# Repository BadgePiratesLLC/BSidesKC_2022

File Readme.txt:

BSidesKC 2022 Website: https://bsideskc.org/

Date: September 23-24, 2021 | PlexPod Westport| Kansas City, MO

LED Layout
------------------
io03 - D1 - "B"
io34 - D2 - "S"
io04 - D3 - "I"
io33 - D4 - "D"
io05 - D5 - "E"
io26 - D6 - "S" (second S)
io06 - D7 - "0"
io21 - D8 - "1" 
io14 - D9 - "2"
io35 - D10 - "3"
io10 - D11 - "4"
io15 - D13 - "5"
io36 - D14 - "6"
io11 - D15 - "7"
io16 - D17 - "8"
io37 - D18 - "9"
io12 - D19 - "10"
io17 - D20 - "11"

Rotary A - 38
Rotary B - 13
Rotary Switch - 7

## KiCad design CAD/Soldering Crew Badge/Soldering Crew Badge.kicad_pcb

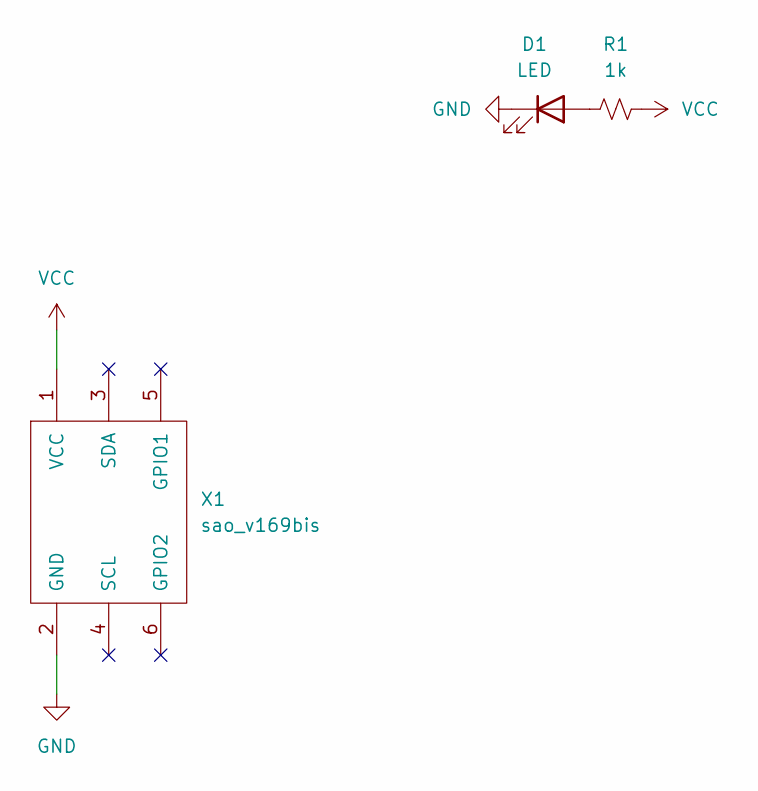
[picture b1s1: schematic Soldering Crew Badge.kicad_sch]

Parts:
D1: LED; LED_Osram_Lx_P47F_D2mm_ReverseMount_Proper_Mask Only
R1: 1k; R_1206_3216Metric
X1: sao_v169bis; Badgelife-SAOv169-SAO_Side_B.SLK

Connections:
GND: D1.1 (K), X1.2 (GND)
unnamed: D1.2 (A), R1.1
VCC: R1.2, X1.1 (VCC)

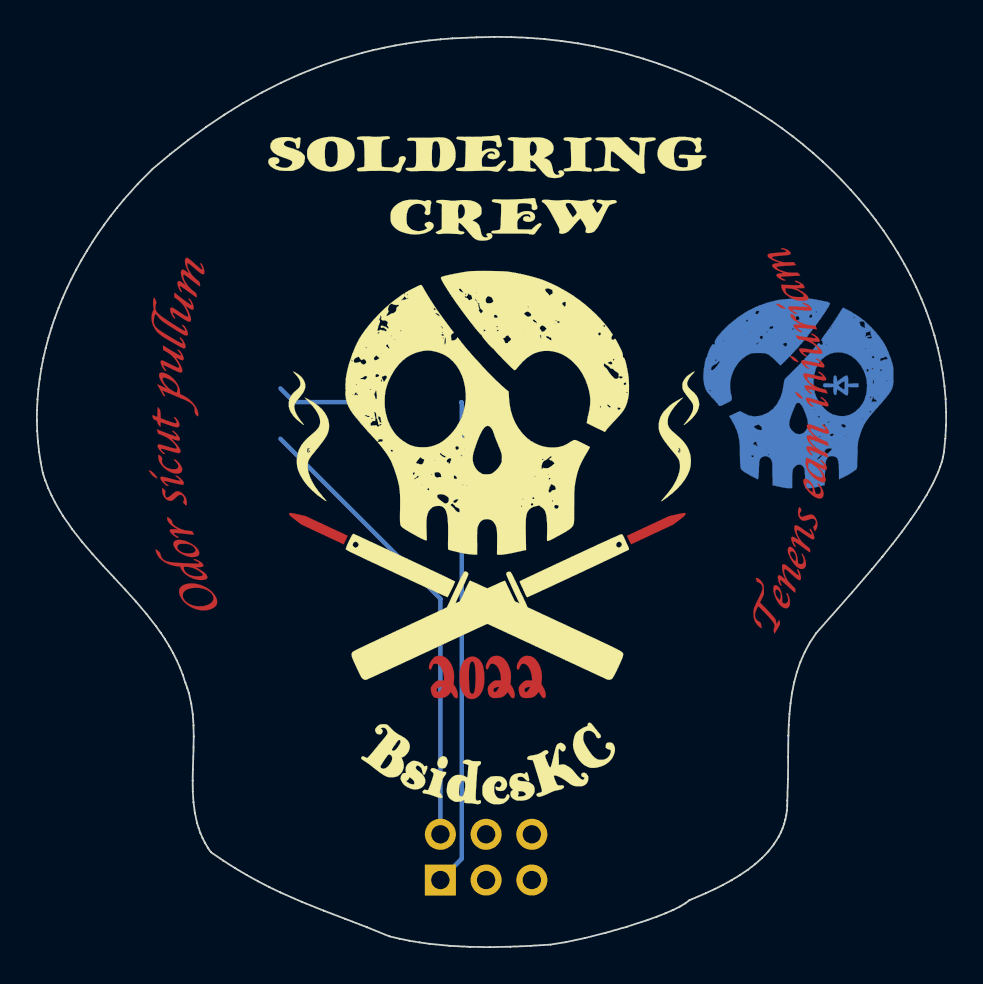
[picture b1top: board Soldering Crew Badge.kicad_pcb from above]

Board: 2 copper layers, 50.5 x 50.6 mm, 3 parts (1 on the bottom side), 3 nets.

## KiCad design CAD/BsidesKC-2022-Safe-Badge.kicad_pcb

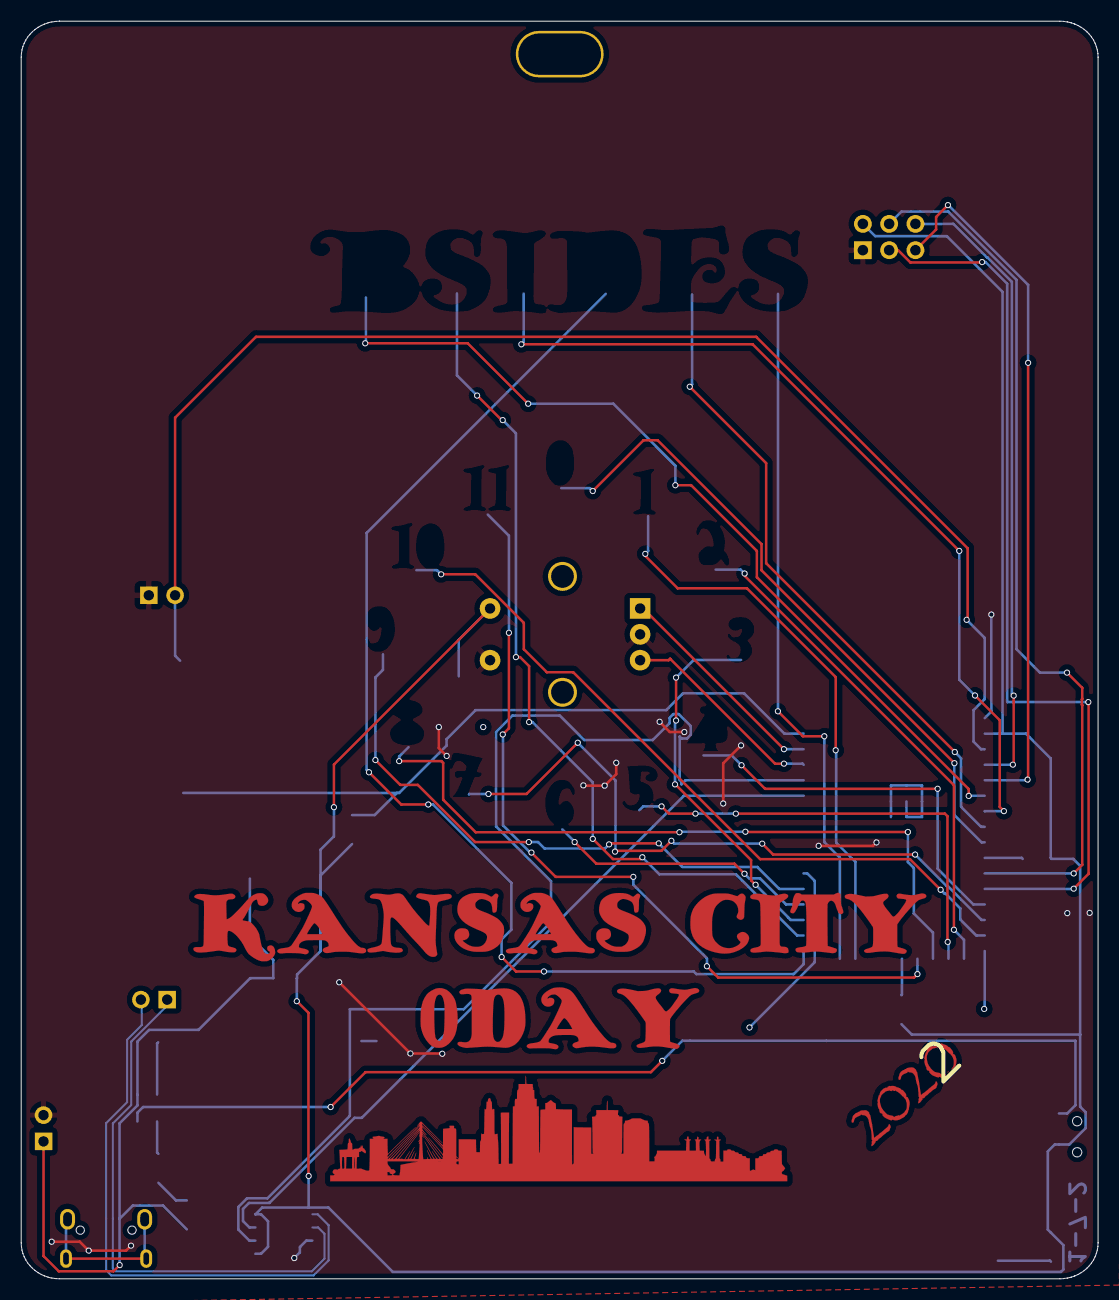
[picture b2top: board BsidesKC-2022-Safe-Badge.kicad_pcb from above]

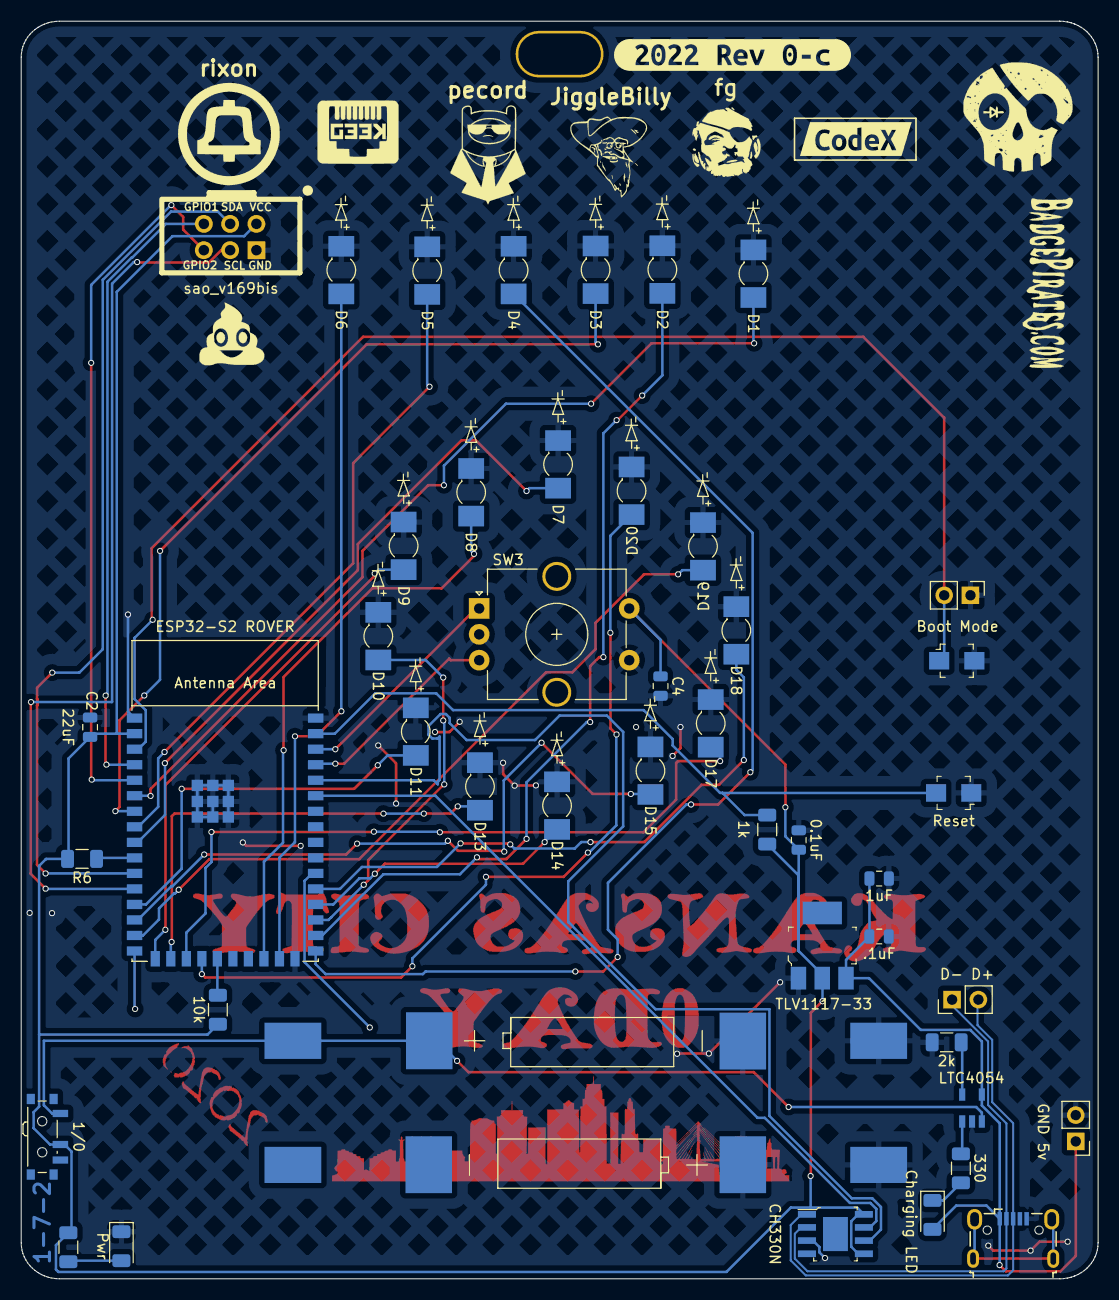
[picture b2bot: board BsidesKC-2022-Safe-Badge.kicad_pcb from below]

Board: 2 copper layers, 104.1 x 121.5 mm, 47 parts (28 on the bottom side), 40 nets.

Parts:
1/0: SW_SPDT; SW_SPDT_PCM12
BT1: Battery; AA
C1: 1uF; C_0805_2012Metric
C2: 22uF; C_0805_2012Metric
C3: 0.1uF; C_0805_2012Metric
C4, C5: .1uF; C_0805_2012Metric
D1, D2, D3, D4, D5, D6, D7, D8, D9, D10, D11, D13, D14, D15, D17, D18, D19, D20: LED; LED_Osram_Lx_P47F_D2mm_ReverseMount_Proper_Mask Only
D12: Charging LED; LED_1206_3216Metric
D16: Pwr; LED_1206_3216Metric
D- D+: Conn_01x02_Female; PinHeader_1x02_P2.54mm_Vertical
ESP32-S2 ROVER: ESP32-S2-WROOM; ESP32-S2-WROVER
GND 5v: 1x2; PinHeader_1x02_P2.54mm_Vertical
J2: 1x2; PinHeader_1x02_P2.54mm_Vertical
J4: USB_B_Mini; USB_Micro-B_Wuerth
R1: 2k; R_1206_3216Metric
R2: 330; R_1206_3216Metric
R3: R; R_1206_3216Metric
R4: 1k; R_1206_3216Metric
R5: 10k; R_1206_3216Metric
R6: R_Small_US; R_1206_3216Metric
Reset: Reset_Btn; Switch_Tactile_SMD_B3U-1000P-BPVersion
SW2: Boot Mode; Switch_Tactile_SMD_B3U-1000P-BPVersion
SW3: RotaryEncoder_Switch; RotaryEncoder_Alps_EC12E-Switch_Vertical_H20mm_CircularMoun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
U1: LTC4054
U3: CH330N; SOIC-8-1EP_W3.9mm
U4: TLV1117-33; SOT-223
X1: sao_v169bis; Badgelife-SAOv169-SAO_Side_B.SLK
kibuzzard-62C240C4: G***; kibuzzard-62C240C4
kibuzzard-62FC3E66: G***; kibuzzard-62FC3E66

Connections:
Boot: ESP32-S2 ROVER.3 (IO00), J2.2, SW2.1 (A)
D+: D- D+.2, J4.3 (D+), U3.1 (UD+)
D-: D- D+.1, J4.2 (D-), U3.2 (UD-)
GND: BT1.2 (-), C1.2, C2.2, C3.2, C4.2, C5.2, D1.1 (K), D2.1 (K), D3.1 (K), D4.1 (K), D5.1 (K), D6.1 (K), D7.1 (K), D8.1 (K), D9.1 (K), D10.1 (K), D11.1 (K), D13.1 (K), D14.1 (K), D15.1 (K), D16.1 (K), D17.1 (K), D18.1 (K), D19.1 (K), D20.1 (K), ESP32-S2 ROVER.1 (GND), ESP32-S2 ROVER.26 (GND), ESP32-S2 ROVER.42 (GND), ESP32-S2 ROVER.43 (GND), GND 5v.2, J2.1, J4.5 (GND), R1.2, Reset.1 (C), SW2.2 (B), SW3.C, SW3.S2, U1.2 (GND), U3.3 (GND), U4.1 (GND), X1.2 (GND)
IO01: ESP32-S2 ROVER.4 (IO01), X1.5 (GPIO1)
IO02: ESP32-S2 ROVER.5 (IO02), X1.6 (GPIO2)
IO03: D1.2 (A), ESP32-S2 ROVER.6 (IO03)
IO04: D3.2 (A), ESP32-S2 ROVER.7 (IO04)
IO05: D5.2 (A), ESP32-S2 ROVER.8 (IO05)
IO06: D7.2 (A), ESP32-S2 ROVER.9 (IO06)
IO07: ESP32-S2 ROVER.10 (IO07), R6.1
IO08: ESP32-S2 ROVER.11 (IO08), X1.3 (SDA)
IO09: ESP32-S2 ROVER.12 (IO09), X1.4 (SCL)
IO10: D11.2 (A), ESP32-S2 ROVER.13 (IO10)
IO11: D15.2 (A), ESP32-S2 ROVER.14 (IO11)
IO12: D19.2 (A), ESP32-S2 ROVER.15 (IO12)
IO14: D9.2 (A), ESP32-S2 ROVER.17 (IO14)
IO15: D13.2 (A), ESP32-S2 ROVER.18 (IO15)
IO16: D17.2 (A), ESP32-S2 ROVER.19 (IO16)
IO17: D20.2 (A), ESP32-S2 ROVER.20 (IO17)
IO21: D8.2 (A), ESP32-S2 ROVER.24 (IO21)
IO26: D6.2 (A), ESP32-S2 ROVER.25 (IO26)
IO33: D4.2 (A), ESP32-S2 ROVER.27 (IO33)
IO34: D2.2 (A), ESP32-S2 ROVER.28 (IO34)
IO35: D10.2 (A), ESP32-S2 ROVER.29 (IO35)
IO36: D14.2 (A), ESP32-S2 ROVER.30 (IO36)
IO37: D18.2 (A), ESP32-S2 ROVER.31 (IO37)
IO45: ESP32-S2 ROVER.39 (IO45), SW3.B
IO46: ESP32-S2 ROVER.40 (IO46), SW3.A
unnamed: 1/0.1 (A), BT1.1 (+), U1.3 (BAT)
unnamed: D12.1 (K), R2.1
unnamed: D16.2 (A), R3.2
unnamed: R1.1, U1.5 (PROG)
unnamed: R2.2, U1.1 (~CHRG)
unnamed: ESP32-S2 ROVER.21 (IO18), R5.1
RESET: ESP32-S2 ROVER.41 (EN), R4.2, Reset.2 (D)
USB_RX_ESP_TX: ESP32-S2 ROVER.37 (TXD0), U3.7 (RXD)
USB_TX_ESP_RX: ESP32-S2 ROVER.38 (RXD0), U3.6 (TXD)
VBUS: C1.1, C5.1, D12.2 (A), GND 5v.1, J4.1 (VBUS), U1.4 (VCC), U4.3 (VI)
VCC: 1/0.2 (B), C2.1, C3.1, C4.1, ESP32-S2 ROVER.2 (3V3), R3.1, R4.1, R5.2, R6.2, SW3.S1, U3.5 (VCC), U3.8 (V3), U4.2 (VO), X1.1 (VCC)

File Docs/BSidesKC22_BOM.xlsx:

Id | DNP | Description | Package | Quantity | Designation | Supplier and ref | Supplier #2 | Cost (at scale) | 1-200 | Total Cost | Notes
1 |  | Resister | R_1206_3216Metric | 20 | 1k |  |  | 0.02 | 0.05 | 0.4
2 | Y |  | PinHeader_1x04_P2.54mm_Vertical | 1 | BottomToTop#1 |  |  |  |  | 0
3 |  | Capacitor | C_0805_2012Metric | 1 | 1uF |  |  | 0.05 | 0.1 | 0.05
4 |  | Resister | R_1206_3216Metric | 1 | 10k |  |  | 0.02 | 0.05 | 0.02
5 |  | LED | LED_1206_3216Metric (yellow) | 1 | Charging |  | https://lcsc.com/search?q=LED%201206 | 0.01 | 0.23 | 0.01
6 |  | MCU | ESP32-S2-WROOM | 1 | ESP32-S2-WROVER | <LUCY> |  | 2.9 | 2.9 | 2.9
7 | Y |  | PinHeader_1x02_P2.54mm_Vertical | 1 | 5v GND |  |  |  |  | 0
8 |  | LED | XZMYK45WT-9 | 18 | LED | https://www.digikey.com/en/products/detail/sunled/XZMYK45WT-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 |  | 0.18 | 0.25 | 3.2399999999999998
9 |  | Push Button | Switch_Tactile_SMD_B3U-1000P | 1 | Reset |  | https://lcsc.com/product-detail/Tactile-Switches_Omron-Elect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 | 0.45 | 0.5 | 0.45
10 | Y |  | PinHeader_1x02_P2.54mm_Vertical | 1 | D+ D- |  |  |  |  | 0
11 |  | Capacitor | C_0805_2012Metric | 3 | 0.1uF |  |  | 0.05 | 0.1 | 0.15000000000000002
12 |  | IC | SOT-223 | 1 | TLV1117-33 | https://www.mouser.com/c/?q=TLV1117-33 | https://lcsc.com/search?q=TLV1117-33 | 0.23 | 0.5 | 0.23
13 | Y |  | FG_B.SILK | 2 | fg |  |  |  |  | 0
14 |  | USB Connector | USB_Micro-B_Wuerth | 1 | USB_B_Mini | https://www.digikey.com/en/products/detail/w%C3%BCrth-elektr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 | Need another | 1.42 | 1.42 | 1.42
15 | Y |  | PinHeader_1x04_P2.54mm_Vertical | 1 | JTAG |  |  |  |  | 0
16 |  | Battery Holder | AA | 2 | Battery | https://www.digikey.com/en/products/detail/keystone-electron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 |  | 0.25 |  | 0.5
16.100000000000001 |  | Battery | 14500 Battery | 1 | Battery |  |  | ? | ? | ? | need to find
17 |  | Slide Switch | SW_SPDT_PCM12 | 1 | SW_SPDT |  | https://lcsc.com/product-detail/Slide-Switches_C-K-PCM12SMTR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 | 0.48 | 0.5 | 0.48
18 |  | IC | SOIC-8-1EP_W3.9mm | 1 | CH330N | <LUCY> |  | 0.38 | 0.38 | 0.38
19 |  | Resister | R_1206_3216Metric | 1 | 330 |  |  | 0.02 | 0.05 | 0.02
20 |  | Slide Switch | Switch_Tactile_SMD_B3U-1000P | 1 | Boot |  | https://lcsc.com/product-detail/Tactile-Switches_Omron-Elect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 | 0.45 | 0.5 | 0.45
21 | Y |  | BPSkull_Distressed_B.SILK | 2 | BP Logo |  |  |  |  | 0
22 |  | IC | MCP73831 | 1 | MCP73831 | https://www.mouser.com/c/?q=mcp%2073831 | https://lcsc.com/product-detail/Battery-Management-ICs_Micro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 | 0.57999999999999996 | 0.69 | 0.57999999999999996
23 | Y |  | BadgePiratesURL_B.SLK | 2 | LOGO |  |  |  |  | 0
24 | Y |  | PinHeader_1x02_P2.54mm_Vertical | 1 | Boot Jumper |  |  |  |  | 0
25 | Y |  | Badgelife-SAOv169-SAO_Side_B.SLK | 1 | sao_v169bis |  |  |  |  | 0
26 |  | Capacitor | C_0805_2012Metric | 1 | 22uF |  |  | 0.05 | 0.1 | 0.05
27 |  | Resister | R_1206_3216Metric | 1 | 2k |  |  | 0.02 | 0.06 | 0.02
28 |  | LED | LED_1206_3216Metric (Green) | 1 | Pwr |  |  | 0.01 | 0.25 | 0.01
29 | Y |  | PinHeader_1x04_P2.54mm_Vertical | 1 | TopToBottom#2 |  |  |  |  | 0
 |  |  |  |  |  |  |  | Just Board Cost |  |  | 0 |  | 0 | 0 | 0
 |  |  |  |  |  |  |  | Profit |  |  | 0 |  | 0 | 0 | 0

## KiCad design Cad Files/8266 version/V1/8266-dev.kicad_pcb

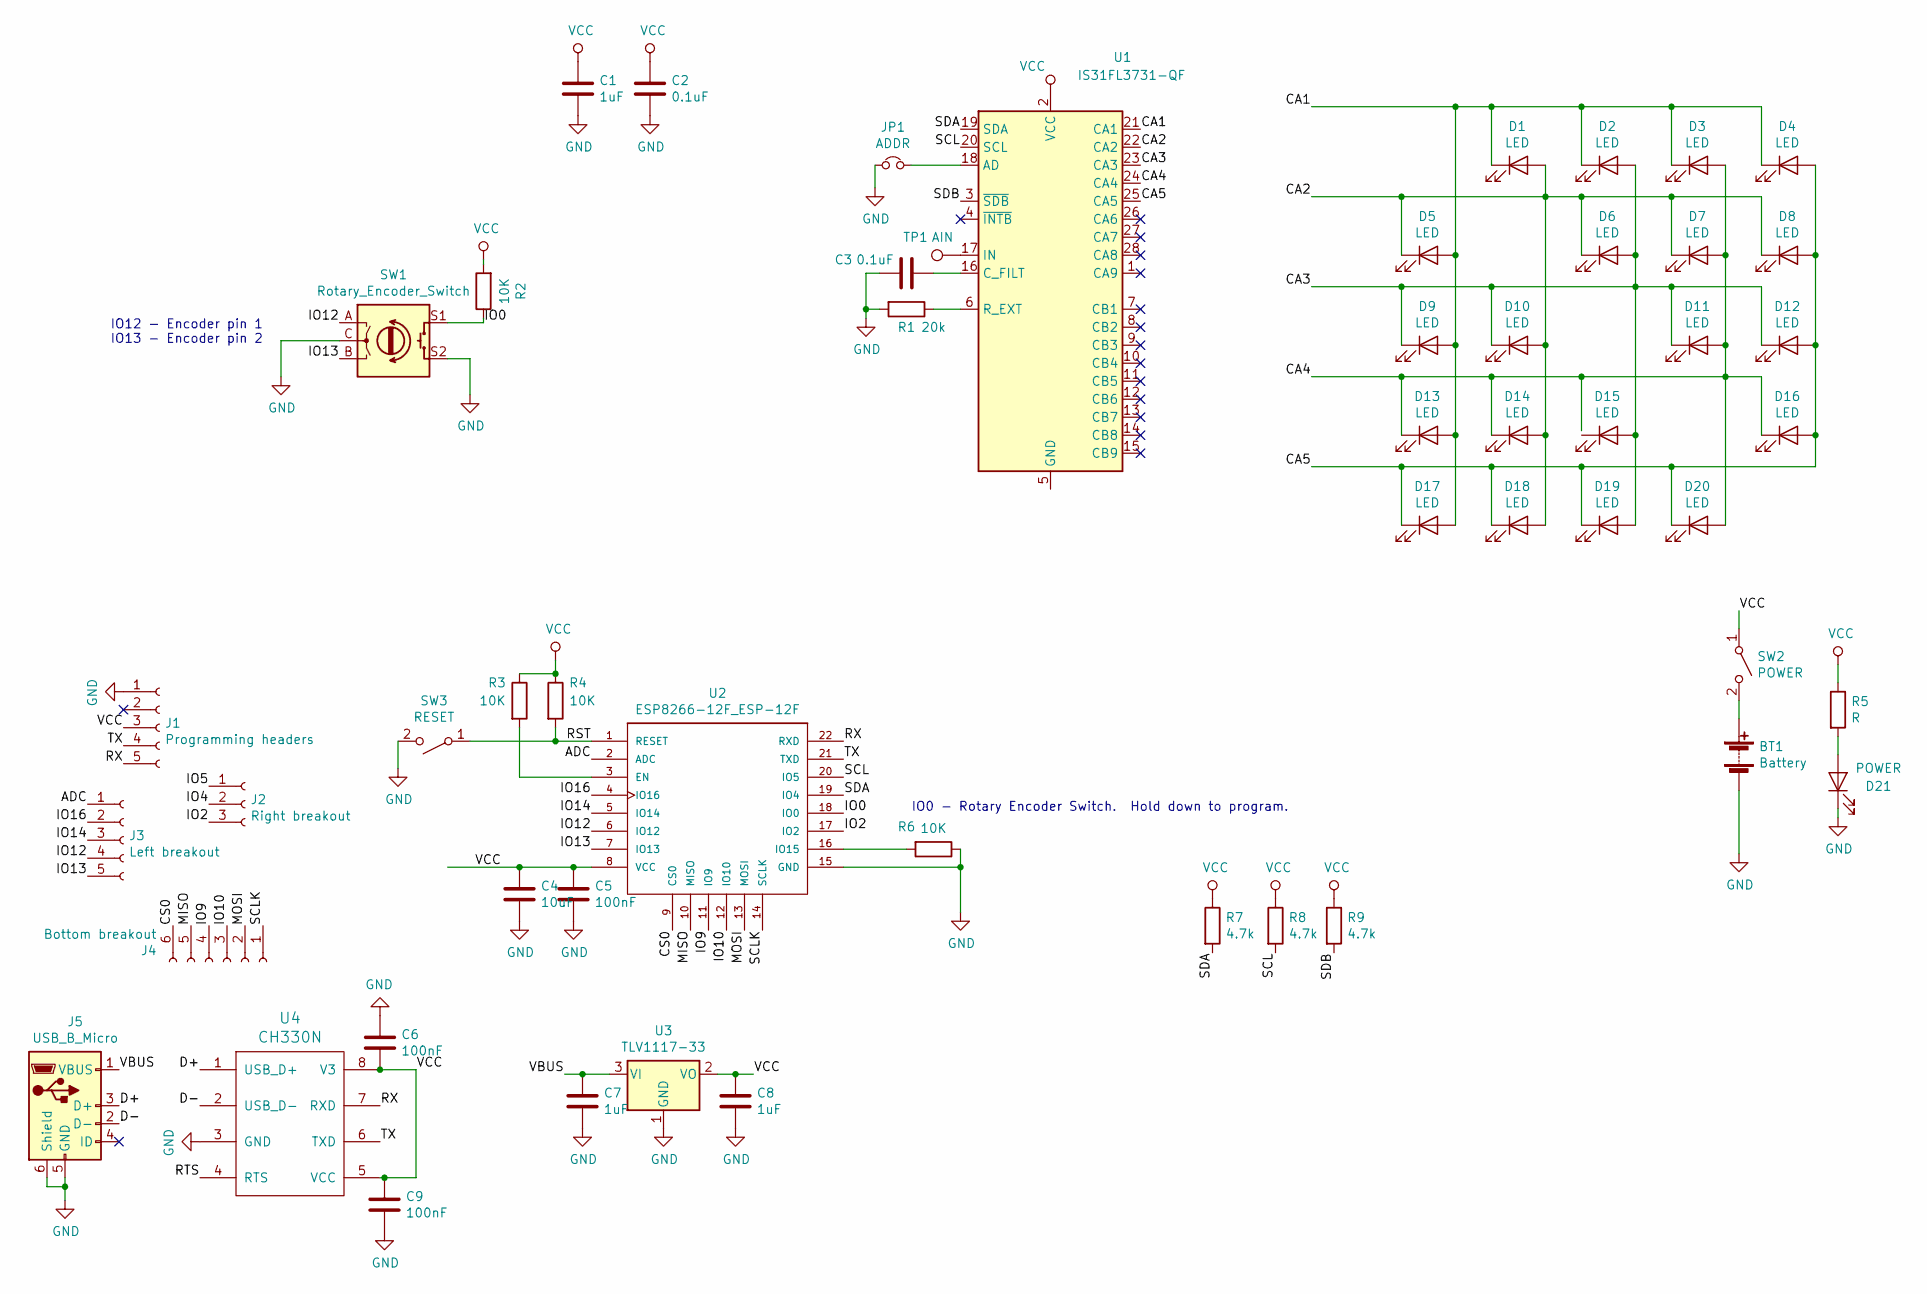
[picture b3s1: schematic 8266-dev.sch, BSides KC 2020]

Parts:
BT1: Battery; BatteryHolder_MPD_BC2003_1x2032
C1, C7, C8: 1uF; C_1206_3216Metric
C2, C3: 0.1uF; C_1206_3216Metric
C4: 10uF; C_1206_3216Metric
C5, C6, C9: 100nF; C_1206_3216Metric
D1, D2, D3, D4, D5, D6, D7, D8, D9, D10, D11, D12, D13, D14, D15, D16, D17, D18, D19, D20: LED; LED_Osram_Lx_P47F_D2mm_ReverseMount
D21: POWER; LED_1206_3216Metric_Pad1.42x1.75mm_HandSolder
J1: Programming headers; PinHeader_1x5_P2.5mm_Drill1.1mm
J2: Right breakout; PinHeader_1x3_P2.54_Drill1.1mm
J3: Left breakout; PinHeader_1x5_P2.5mm_Drill1.1mm
J4: Bottom breakout; PinHeader_1x06_P2.54mm_Vertical
J5: USB_B_Micro; USB_Micro-B_Molex-105017-0001
JP1: ADDR; SolderJumper-2_P1.3mm_Bridged_Pad1.0x1.5mm
R1: 20k; R_1206_3216Metric
R2, R3, R4, R6: 10K; R_1206_3216Metric
R5: R; R_1206_3216Metric
R7, R8, R9: 4.7k; R_1206_3216Metric
SW1: Rotary_Encoder_Switch; RotaryEncoder_Alps_EC12E-Switch_Vertical_H20mm_CircularMoun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
SW2: POWER; SW_SPDT_PCM12
SW3: RESET; SW_Push_1P1T_NO_6x6mm_H9.5mm
TP1: AIN; TestPoint_Pad_D2.0mm
U1: IS31FL3731-QF; QFN-28-1EP_4x4mm_P0.4mm_EP2.3x2.3mm
U2: ESP8266-12F_ESP-12F; XCVR_ESP8266-12E%2fESP-12E
U3: TLV1117-33; SOT-223-3_TabPin2
U4: CH330N; SOIC-8_3.9x4.9mm_P1.27mm

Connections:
/ADC: J3.1, U2.2 (ADC)
/CA1: D1.1 (K), D2.1 (K), D3.1 (K), D4.1 (K), D5.2 (A), D9.2 (A), D13.2 (A), D17.2 (A), U1.21 (CA1)
/CA2: D1.2 (A), D5.1 (K), D6.1 (K), D7.1 (K), D8.1 (K), D10.2 (A), D14.2 (A), D18.2 (A), U1.22 (CA2)
/CA3: D2.2 (A), D6.2 (A), D9.1 (K), D10.1 (K), D11.1 (K), D12.1 (K), D15.2 (A), D19.2 (A), U1.23 (CA3)
/CA4: D3.2 (A), D7.2 (A), D11.2 (A), D13.1 (K), D14.1 (K), D16.1 (K), D20.2 (A), U1.24 (CA4)
/CA5: D4.2 (A), D8.2 (A), D12.2 (A), D16.2 (A), D17.1 (K), D18.1 (K), D19.1 (K), D20.1 (K), U1.25 (CA5)
/CS0: J4.6, U2.9 (CS0)
/D+: J5.3 (D+), U4.1 (USB_D+)
/D-: J5.2 (D-), U4.2 (USB_D-)
/IO0: R2.1, SW1.S1, U2.18 (IO0)
/IO2: J2.3, U2.17 (IO2)
/IO9: J4.4, U2.11 (IO9)
/IO10: J4.3, U2.12 (IO10)
/IO12: J3.4, SW1.A, U2.6 (IO12)
/IO13: J3.5, SW1.B, U2.7 (IO13)
/IO14: J3.3, U2.5 (IO14)
/IO16: J3.2, U2.4 (IO16)
/MISO: J4.5, U2.10 (MISO)
/MOSI: J4.2, U2.13 (MOSI)
/RST: R4.2, SW3.1 (A), U2.1 (RESET)
/RTS: U4.4 (RTS)
/RX: J1.5, U2.22 (RXD), U4.7 (RXD)
/SCL: R8.2, U1.20 (SCL), U2.20 (IO5)
/SCLK: J4.1, U2.14 (SCLK)
/SDA: R7.2, U1.19 (SDA), U2.19 (IO4)
/SDB: R9.2, U1.3 (~SDB)
/TX: J1.4, U2.21 (TXD), U4.6 (TXD)
/VBUS: C7.1, J5.1 (VBUS), U3.3 (VI)
GND: BT1.2 (-), C1.2, C2.2, C3.2, C4.2, C5.2, C6.1, C7.2, C8.2, C9.2, D21.1 (K), J1.1, J5.5 (GND), J5.6 (Shield), JP1.1, R1.2, R6.1, SW1.C, SW1.S2, SW3.2 (B), U2.15 (GND), U3.1 (GND), U4.3 (GND)
unnamed: BT1.1 (+), SW2.2 (B)
unnamed: C3.1, U1.16 (C_FILT)
unnamed: D21.2 (A), R5.2
unnamed: JP1.2, U1.18 (AD)
unnamed: R1.1, U1.6 (R_EXT)
unnamed: R3.2, U2.3 (EN)
unnamed: R6.2, U2.16 (IO15)
unnamed: TP1.1, U1.17 (IN)
unnamed: U1.5 (GND), U1.29 (GND)
VCC: C1.1, C2.1, C4.1, C5.1, C6.2, C8.1, C9.1, J1.3, R2.2, R3.1, R4.1, R5.1, R7.1, R8.1, R9.1, SW2.1 (A), U1.2 (VCC), U2.8 (VCC), U3.2 (VO), U4.5 (VCC), U4.8 (V3)

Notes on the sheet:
IO0 - Rotary Encoder Switch. Hold down to program.
IO12 - Encoder pin 1 IO13 - Encoder pin 2

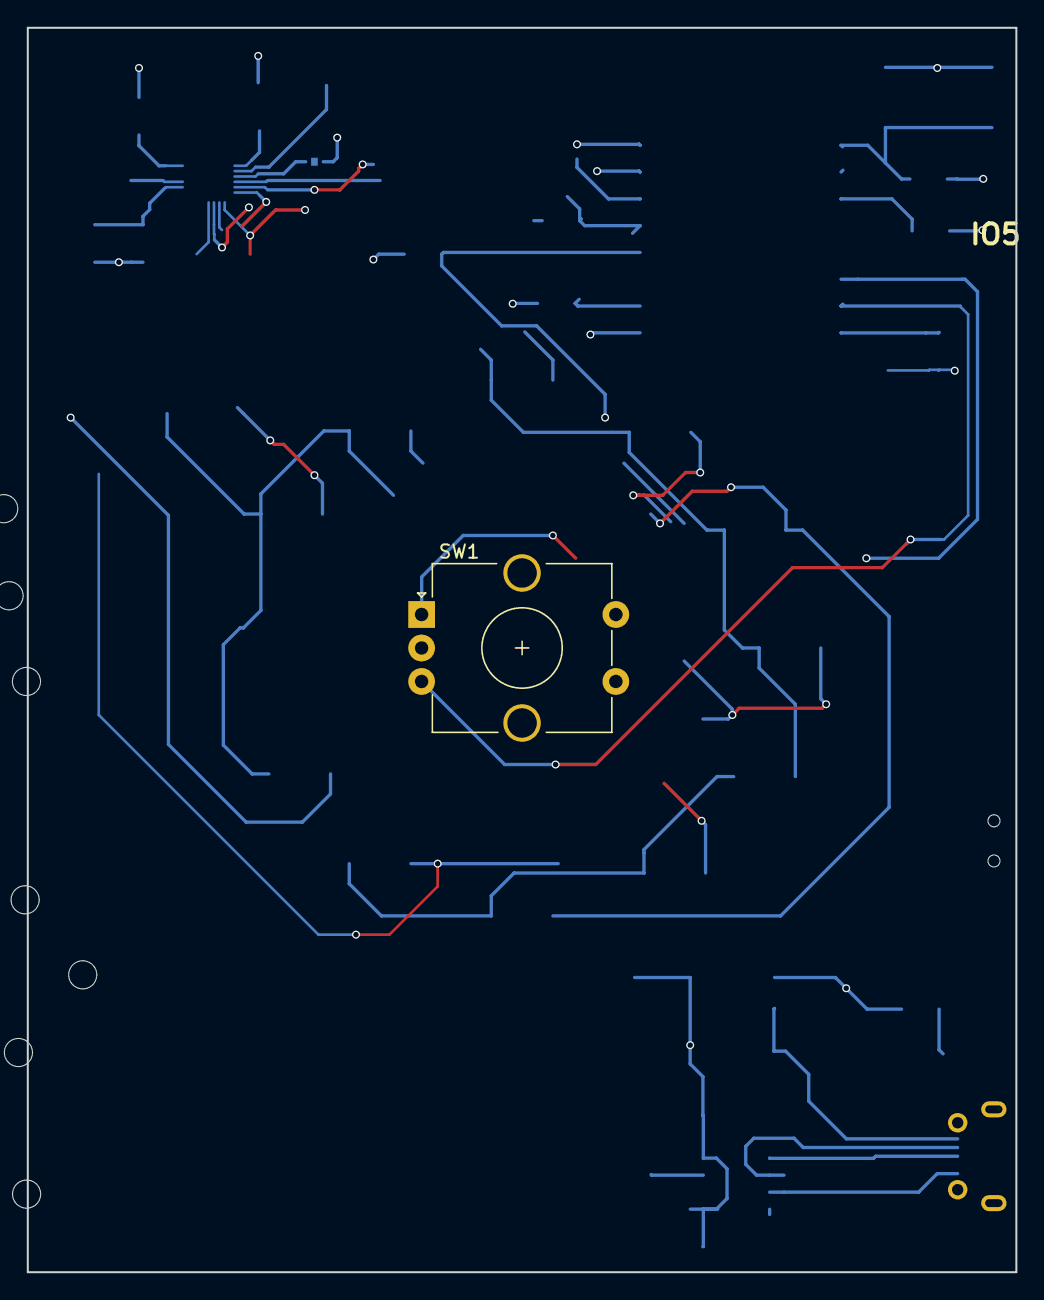
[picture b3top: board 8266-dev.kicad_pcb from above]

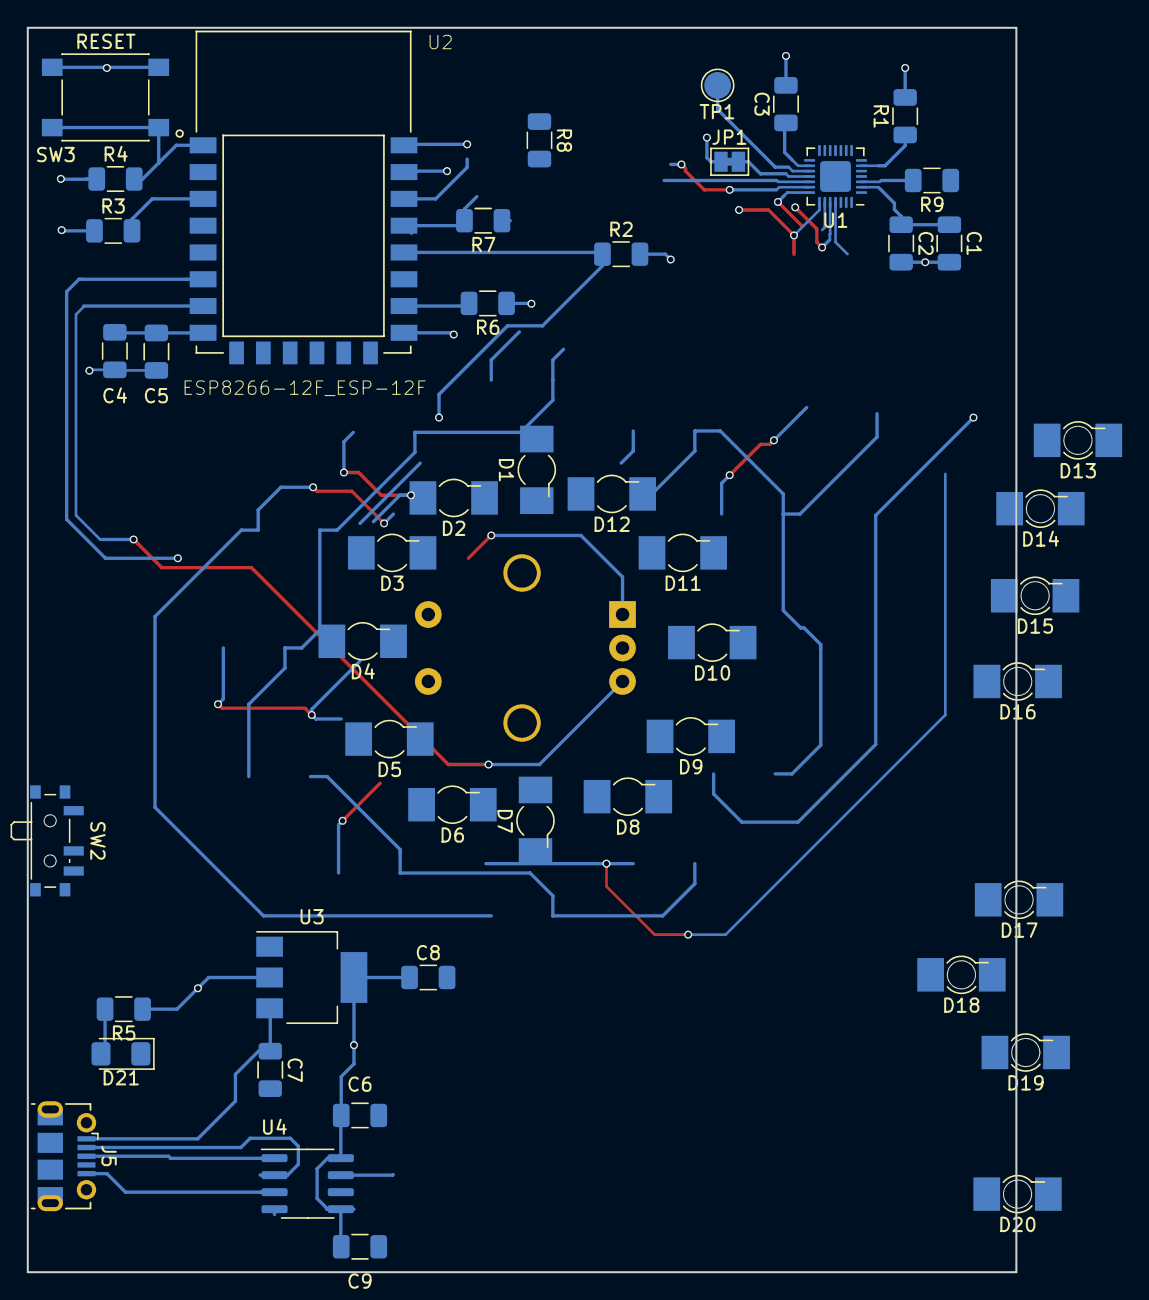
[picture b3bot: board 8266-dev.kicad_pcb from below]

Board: 2 copper layers, 73.8 x 92.9 mm, 51 parts (48 on the bottom side), 27 nets.

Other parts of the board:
ART001: Front; SafeFrontMask
ART002: Back; SafeBackMask

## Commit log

2021-09-27 adding S2 Files
2022-07-02 Artwork housekeeping
    Cleaned up Artwork Folder
    Initial clean up/mods to safe artwork to prep for 2022 version
2022-07-02 Artwork updated + CAD Export
    Reformated artwork + resize
    Exported to CAD
2022-07-04 adding and taking away
    Adding electronics to boards, and removing old builds.
2022-08-17 fixing footprint and fill
2022-08-18 adding silk layer
2022-08-19 fixes
    Fixing silk, and adding headers
2022-08-19 adding R
2022-08-19 Gerbers and a single trace move
2022-08-19 gerbers
2022-08-20 Making China Happy with Back Mask
2022-08-21 adding WKS
2022-08-21 added source code, just the platformio.ini file and a basic main.cpp for now
2022-08-22 cycle through all lights
2022-08-31 fixing rotatry messup
2022-09-02 Artwork Updates
    Added artwork/pretty files for each version of the badge
    Updated Moon SAO and added pretty files
    Created sample of the BsidesKC2022 shirt logo/poster
2022-09-02 encoder turns the lights
2022-09-02 versions and gerbers
2022-09-02 cleanup
2022-09-02 improve encoder performance
    While spinning the encoded fast I was able to cause it to lock up repeatedly. I looked at the example code and noticed they had a way of detecting direction as a 1 or -1 and I decided to use that to 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
2022-09-02 clean up, add bling code
2022-09-02 Gold SAO artwork/CAD
    Completed Gold vendor designs
2022-09-03 Village Badge
2022-09-03 village update
2022-09-03 inline bling code
    it takes up a lot of LoC so I just inlined the write and delay calls for now to condense it a bit
2022-09-03 init state machine
2022-09-03 clean up
2022-09-03 fix indention
2022-09-04 added alignment marks
2022-09-04 add back in bling mode
    this does bling mode without using delays, it takes in the current run time and figures out if it should advance to the next part of the animation. broke input mode somehow but we should be able to f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
2022-09-04 button push works!
2022-09-05 click to change bling working
2022-09-05 found where to hook in to capture selected number and log it plus lots of other stuff
2022-09-05 codes are working!
2022-09-05 reset userInput and inputPosition on transition back to bling mode and turn off all LEDs when transitioning to input mode
2022-09-05 more cleanup
2022-09-05 add a constants and pins file
2022-09-06 Sao Creations
2022-09-06 move rotary switch over to pin.h
2022-09-06 Resized BsidesKC SAO
2022-09-06 Soldering Village-Crew Badge
2022-09-06 Cutout eye for Soldering Village badge
2022-09-07 Resized/Updated Soldering Village SAO
2022-09-07 Order Tracking Sheet
2022-09-07 soa and doc updates
2022-09-07 BsidesKC 2022 Badge Schematic PCB
2022-09-09 added pwm test
2022-09-09 fix rotary encoder turning by reverting pin.h and constant.h
2022-09-10 fix constants
2022-09-10 add codes
2022-09-10 eeprom save
2022-09-10 Update Tracking
2022-09-13 init
2022-09-13 change path to /
2022-09-16 Templates - WIP
    These are templates off of last years, I will update with current Costs and Pricing this weekend.
2022-09-16 updates to Project Summary and Costs
2022-09-18 blah
2022-09-18 CLEANUIP
2022-09-18 use rotary button
2022-09-18 move wifi up
2022-09-18 good enough
2022-09-18 now its good enough
2022-09-19 update help message
2022-09-19 Added HTML BOM View
2022-09-20 wifi timeout
2022-09-20 add credits
2022-09-22 Refactor some stuff
2022-09-22 OTA Firmware updating
2022-09-22 Add call to start updater task
2022-09-22 Update wifi credentials to match plexpod
2022-09-22 Remove mac metadata(.gitignore)
2022-09-23 ESP OTA Update(double click BOOT)
2022-09-23 Add catch for HTTP manifest err
2022-09-23 Correct inverted LED
2022-09-23 low(er) power mode
2022-09-23 Show blink confimation when button is pressed
2022-09-23 confirmation flash on correct code entry
2022-09-23 confirmation flash
2022-09-23 Branch out functions for cleanliness
2022-09-23 Better handling on code errors and input reset triggers
2022-09-23 Badge firmware V3
2022-09-26 doc update
2022-09-28 Removed duplicate Jenny code
    Code block lines 426 to 430 were duplicated below next loop.
2022-09-28 Removed extra ":" to match the rest of the messages
2023-06-07 Create SolidLights.ino
    All lights on test
